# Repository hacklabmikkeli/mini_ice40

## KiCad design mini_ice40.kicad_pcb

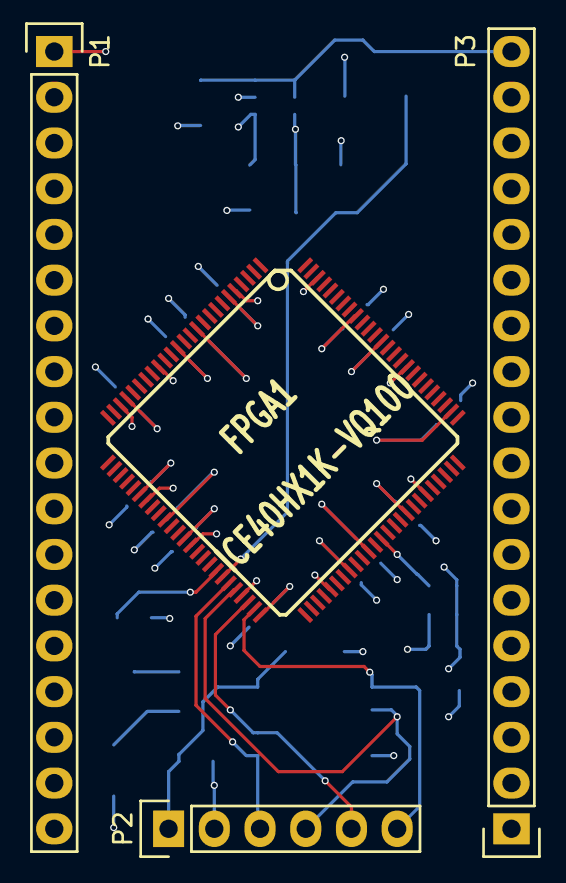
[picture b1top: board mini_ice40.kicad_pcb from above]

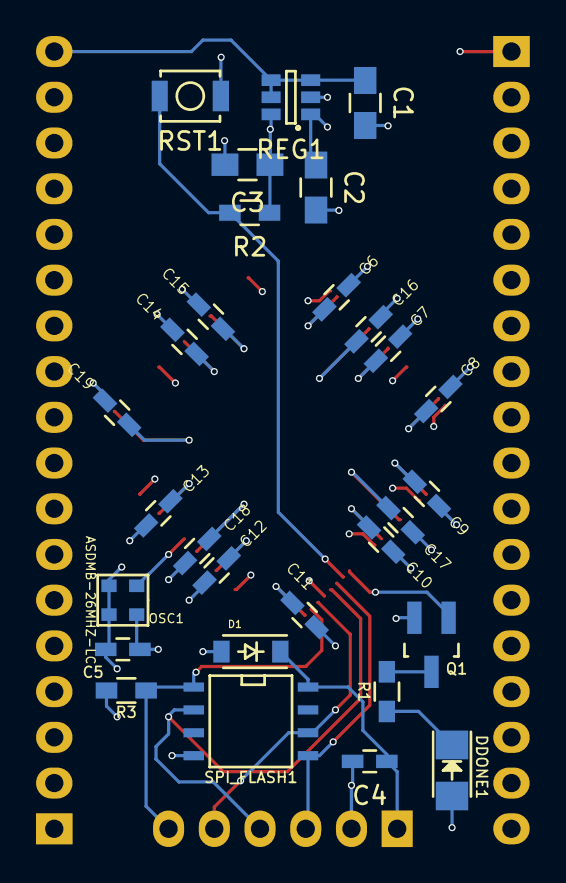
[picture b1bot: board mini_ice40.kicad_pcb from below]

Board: 4 copper layers, 33 parts (29 on the bottom side), 48 nets.

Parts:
C1, C2, C3: 1u; C_0805_HandSoldering
C4, C5, C6, C7, C8, C9, C10, C11, C12, C13, C14, C15, C16, C17, C18, C19: 0u1; C_0603_HandSoldering
D1: 1N4448WQ-7-F; SOD-123
DDONE1: SML-LX1206GC-TR1; LED_1206
FPGA1: ICE40HX1K-VQ100; VQFP100
OSC1: ASDMB-26MHZ-LC; 2MMx2MM5
P1, P3: CONN_01X18; Pin_Header_Straight_1x18
P2: CONN_01X04; Pin_Header_Straight_1x06
Q1: 2N7002LT1G; SOT-23_Handsoldering
R1: 330; R_0603_HandSoldering
R2, R3: 10K; R_0603_HandSoldering
REG1: AP7312-1233W6-7; SOT-23-6
RST1: SW_PUSH; SW_SPST_B3U-1000P
SPI_FLASH1: AT25SF041-SSHD-B; SOIC-8-N

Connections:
+1V2: C3.1, C16.1, C17.1, C18.1, C19.1, FPGA1.11, FPGA1.35, FPGA1.61, FPGA1.77, R2.1, REG1.6
+3V3: C2.1, C5.1, C6.1, C7.1, C8.1, C9.1, C10.1, C11.1, C12.1, C13.1, C14.1, C15.1, D1.2, DDONE1.2, FPGA1.6, FPGA1.14, FPGA1.22, FPGA1.31, FPGA1.38, FPGA1.50, FPGA1.58, FPGA1.67, FPGA1.88, FPGA1.92, OSC1.4, R3.1, REG1.1
GND: C1.2, C2.2, C3.2, C4.2, C5.2, C6.2, C7.2, C8.2, C9.2, C10.2, C11.2, C12.2, C13.2, C14.2, C15.2, C16.2, C17.2, C18.2, C19.2, FPGA1.5, FPGA1.17, FPGA1.23, FPGA1.32, FPGA1.39, FPGA1.47, FPGA1.55, FPGA1.70, FPGA1.84, FPGA1.98, OSC1.1, OSC1.2, P1.1, P2.2, Q1.2, REG1.2, RST1.1, SPI_FLASH1.4
unnamed: C4.1, D1.1, P2.1, SPI_FLASH1.8
unnamed: DDONE1.1, R1.1
unnamed: FPGA1.4, P1.2
unnamed: FPGA1.9, P1.3
unnamed: FPGA1.16, P1.4
unnamed: FPGA1.18, P1.5
unnamed: FPGA1.19, P1.6
unnamed: FPGA1.20, P1.7
unnamed: FPGA1.24, P1.8
unnamed: FPGA1.25, P1.9
unnamed: FPGA1.27, P1.10
unnamed: FPGA1.28, P1.11
unnamed: FPGA1.29, P1.12
unnamed: FPGA1.30, P1.13
unnamed: FPGA1.33, P1.14
unnamed: FPGA1.37, P1.15
unnamed: FPGA1.40, P1.16
unnamed: FPGA1.41, P1.17
unnamed: FPGA1.42, P1.18
unnamed: FPGA1.43, Q1.1
unnamed: FPGA1.44, R2.2, RST1.2
unnamed: FPGA1.45, P2.3, SPI_FLASH1.5
unnamed: FPGA1.46, P2.4, SPI_FLASH1.2
unnamed: FPGA1.48, P2.5, SPI_FLASH1.6
unnamed: FPGA1.49, P2.6, R3.2, SPI_FLASH1.1
unnamed: FPGA1.51, P3.1
unnamed: FPGA1.52, P3.2
unnamed: FPGA1.53, P3.3
unnamed: FPGA1.54, P3.4
unnamed: FPGA1.56, P3.5
unnamed: FPGA1.57, P3.6
unnamed: FPGA1.59, P3.7
unnamed: FPGA1.60, P3.8
unnamed: FPGA1.62, P3.9
unnamed: FPGA1.63, OSC1.3
unnamed: FPGA1.85, P3.10
unnamed: FPGA1.86, P3.11
unnamed: FPGA1.90, P3.12
unnamed: FPGA1.95, P3.13
unnamed: FPGA1.96, P3.14
unnamed: FPGA1.97, P3.15
unnamed: FPGA1.99, P3.16
unnamed: FPGA1.100, P3.17
unnamed: Q1.3, R1.2
VCC: C1.1, P3.18, REG1.3, REG1.4, REG1.5

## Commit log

2016-04-08 ** Initial commit
2016-04-10 ** Switched regulators
2016-04-10 ** Different regulator, decoupling caps
2016-04-11 ** Laid out PCB
2016-04-11 ** Shorter PCB to keep <5cm
2016-04-12 ** 4-layer PCB design
2016-04-12 ** 4-layer PCB sans GPIO
2016-04-12 ** Finished 4-layer PCB layout
2016-04-12 Added LICENSE
